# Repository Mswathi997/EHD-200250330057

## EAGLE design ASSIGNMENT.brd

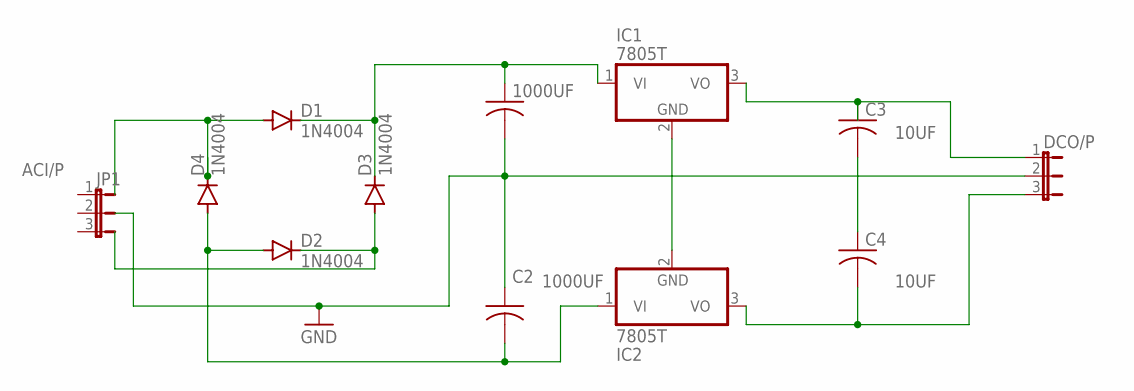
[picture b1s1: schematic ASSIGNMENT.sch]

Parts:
1000UF: C-US050-030X075; C050-030X075
C2, C3, C4: C-US050-030X075; C050-030X075
D1, D2, D3, D4: 1N4004; DO41-10
DCO/P: JP2E; JP2
IC1, IC2: 7805T; TO220H
JP1: JP2E; JP2

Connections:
10UF: C3.2, C4.1, C4.2, DCO/P.3, IC2.3 (VO)
1000UF: C2.2, D2.A, D4.A, IC2.1 (VI)
ACI/P: D1.A, D4.C
GND: 1000UF.2, C2.1, DCO/P.2
unnamed: D2.C, D3.A
unnamed: C3.1, DCO/P.1, IC1.3 (VO)
unnamed: IC1.2 (GND), IC2.2 (GND)
unnamed: 1000UF.1, D1.C, D3.C, IC1.1 (VI)

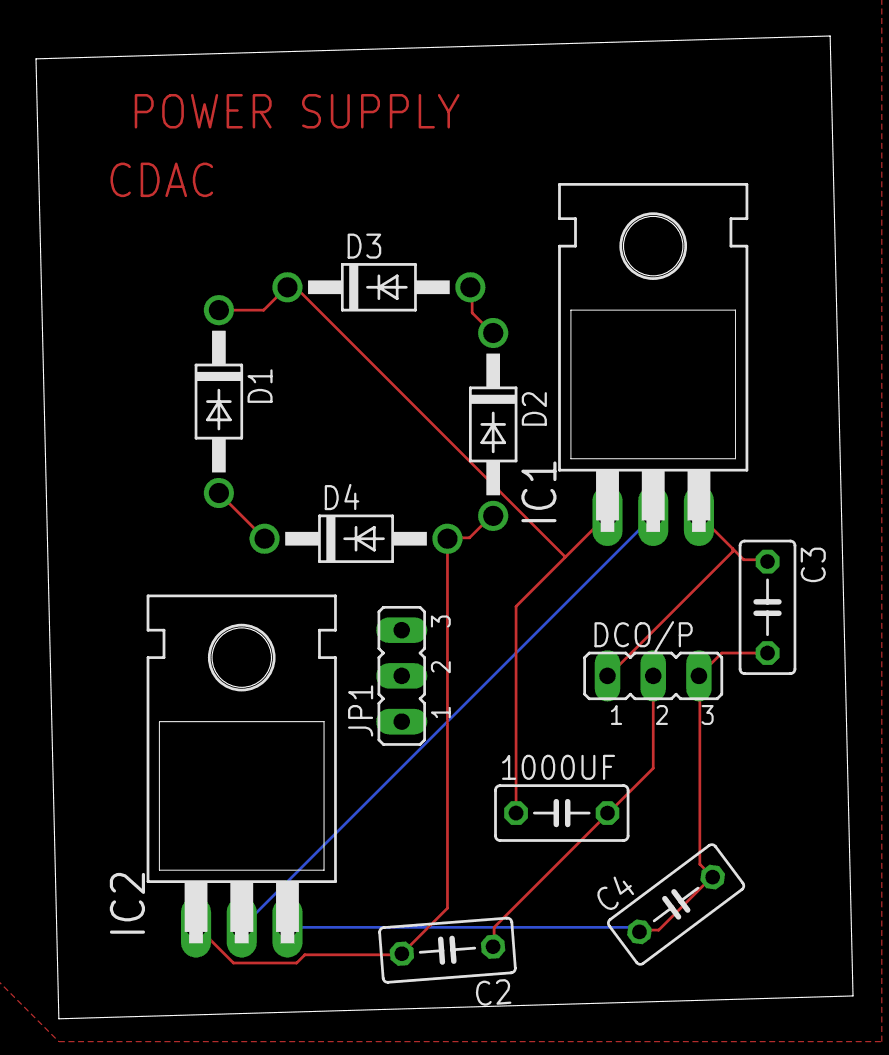
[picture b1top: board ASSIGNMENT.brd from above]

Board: 2 copper layers, 45.4 x 54.6 mm, 12 parts (0 on the bottom side), 8 nets.
